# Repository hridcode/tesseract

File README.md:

# Tesseract

Tesseract is a retro-style MP3 player with audio output to speakers and headphones, an LCD display, and battery charging for on-the-go listening. I made this because I wanted to have a dedicated device to run a library of my favorite music in a simplistic way, as a sort of action against streaming services.

## Features

- 32-bit 48kHz stereo output to speakers and headphones
- microSD card file loading (up to 32GB)
- 2.0" LCD display (ST7789)
- Battery charging with power path
- Album and artist shuffling modes
- Genre tags

## Pictures

|Schematic|PCB|Case|
|---|---|---|
||||

## BOM

|Part|Quantity|Cost|Link|
|---|---|---|---|
|0402 4.7uF capacitor|3|$0.070|[LCSC](https://www.lcsc.com/product-detail/C23733.html)|
|0402 10uF capacitor|10|$0.258|[LCSC](https://www.lcsc.com/product-detail/C15525.html)|
|0603 22uF capacitor|3|$0.094|[LCSC](https://www.lcsc.com/product-detail/C59461.html)|
|0402 0.1uF capacitor|18|$0.099|[LCSC](https://www.lcsc.com/product-detail/C1525.html)|
|0402 2.2uF capacitor|4|$0.026|[LCSC](https://www.lcsc.com/product-detail/C12530.html)|
|0402 0.47uF capacitor|2|$0.028|[LCSC](https://www.lcsc.com/product-detail/C47339.html)|
|0402 20pF capacitor|2|$0.016|[LCSC](https://www.lcsc.com/product-detail/C1554.html)|
|0402 1uF capacitor|1|$0.012|[LCSC](https://www.lcsc.com/product-detail/C52923.html)|
|microSD card receptacle|1|$0.061|[LCSC](https://www.lcsc.com/product-detail/C7529389.html)|
|0402 3.3uH inductor|1|$0.076|[LCSC](https://www.lcsc.com/product-detail/C48946153.html)|
|0402 1uH inductor|1|$0.035|[LCSC](https://www.lcsc.com/product-detail/C22400378.html)|
|0402 5.1KΩ resistor|2|$0.005|[LCSC](https://www.lcsc.com/product-detail/C25905.html)|
|0402 470Ω resistor|2|$0.010|[LCSC](https://www.lcsc.com/product-detail/C25117.html)|
|0603 20KΩ resistor|2|$0.008|[LCSC](https://www.lcsc.com/product-detail/C4184.html)|
|0402 10Ω resistor|1|$0.003|[LCSC](https://www.lcsc.com/product-detail/C25077.html)|
|0402 10KΩ resistor|4|$0.019|[LCSC](https://www.lcsc.com/product-detail/C25531.html)|
|0603 27Ω resistor|2|$0.007|[LCSC](https://www.lcsc.com/product-detail/C25190.html)|
|0402 33Ω resistor|1|$0.008|[LCSC](https://www.lcsc.com/product-detail/C25105.html)|
|0402 1KΩ resistor|2|$0.008|[LCSC](https://www.lcsc.com/product-detail/C11702.html)|
|0603 2Ω resistor|2|$0.006|[LCSC](https://www.lcsc.com/product-detail/C22977.html)|
|USB-C receptacle|1|$0.172|[LCSC](https://www.lcsc.com/product-detail/C165948.html)|
|12-pin 0.5mm pitch FPC connector|1|$0.088|[LCSC](https://www.lcsc.com/product-detail/C51901313.html)|
|ST7789 12-pin display|1|$4.060|[AliExpress](https://www.aliexpress.us/item/3256810577766519.html)|
|RP2354A|1|$1.318|[LCSC](https://www.lcsc.com/product-detail/C41378174.html)|
|PCM5102A|1|$1.416|[LCSC](https://www.lcsc.com/product-detail/C107671.html)|
|PAM8403D|1|$0.267|[LCSC](https://www.lcsc.com/product-detail/C5122557.html)|
|PJ-242 switching audio jack|1|$0.138|[LCSC](https://www.lcsc.com/product-detail/C431536.html)|
|8Ω 0.5W 20mm speaker|1|$2.690|[AliExpress](https://www.aliexpress.us/item/3256809939513877.html)|
|IP5306|1|$0.299|[LCSC](https://www.lcsc.com/product-detail/C181692.html)|
|XC6206P332MR|1|$0.147|[LCSC](https://www.lcsc.com/product-detail/C5446.html)|
|3.7V 2000mAh lithium polymer battery|1|$6.990|[AliExpress](https://www.aliexpress.us/item/3256802733222186.html)|
|AS5600-ASOT|1|$1.436|[LCSC](https://www.lcsc.com/product-detail/C499458.html)|
|Diametric magnet|1|$0.199|[AliExpress](https://www.aliexpress.us/item/3256810578708839.html)|
|2x1mm neodymium magnets|50|$3.220|[AliExpress](https://www.aliexpress.us/item/3256811645736463.html)|
|12MHz 20pF crystal oscillator|1|$0.096|[LCSC](https://www.lcsc.com/product-detail/C9002.html)|
|3-pin SPDT slide switch|1|$4.950|[AliExpress](https://www.aliexpress.us/item/3256809632258636.html)|
|PCB|1|$1.400|[JLCPCB](https://cart.jlcpcb.com/quote?stencilLayer=4&stencilWidth=65&stencilLength=100&stencilCounts=5&plateType=1&spm=Jlcpcb.Homepage.1010)|
|Resin printed parts|5|$8.640|[JLC3DP](https://jlc3dp.com/3d-printing-quote?queryMaterialTechnicsId=1)|
|**Total**||**$40.166**||

## Notes

You can visit the Onshape project [here](https://cad.onshape.com/documents/0cda69ddcaf8f9abaf0bc503/w/b4a9e0f35602d26ad8b0afbe/e/33b76f34621fe33578d60277?renderMode=0&uiState=6a938bd5edeed672aad4ec0b).

The PCB is 4 layers (SIG/GND/PWR/SIG).

The firmware is still being developed. I will work on making it better once the device is fully built.

I plan on getting this assembled, hopefully it's not too expensive :(

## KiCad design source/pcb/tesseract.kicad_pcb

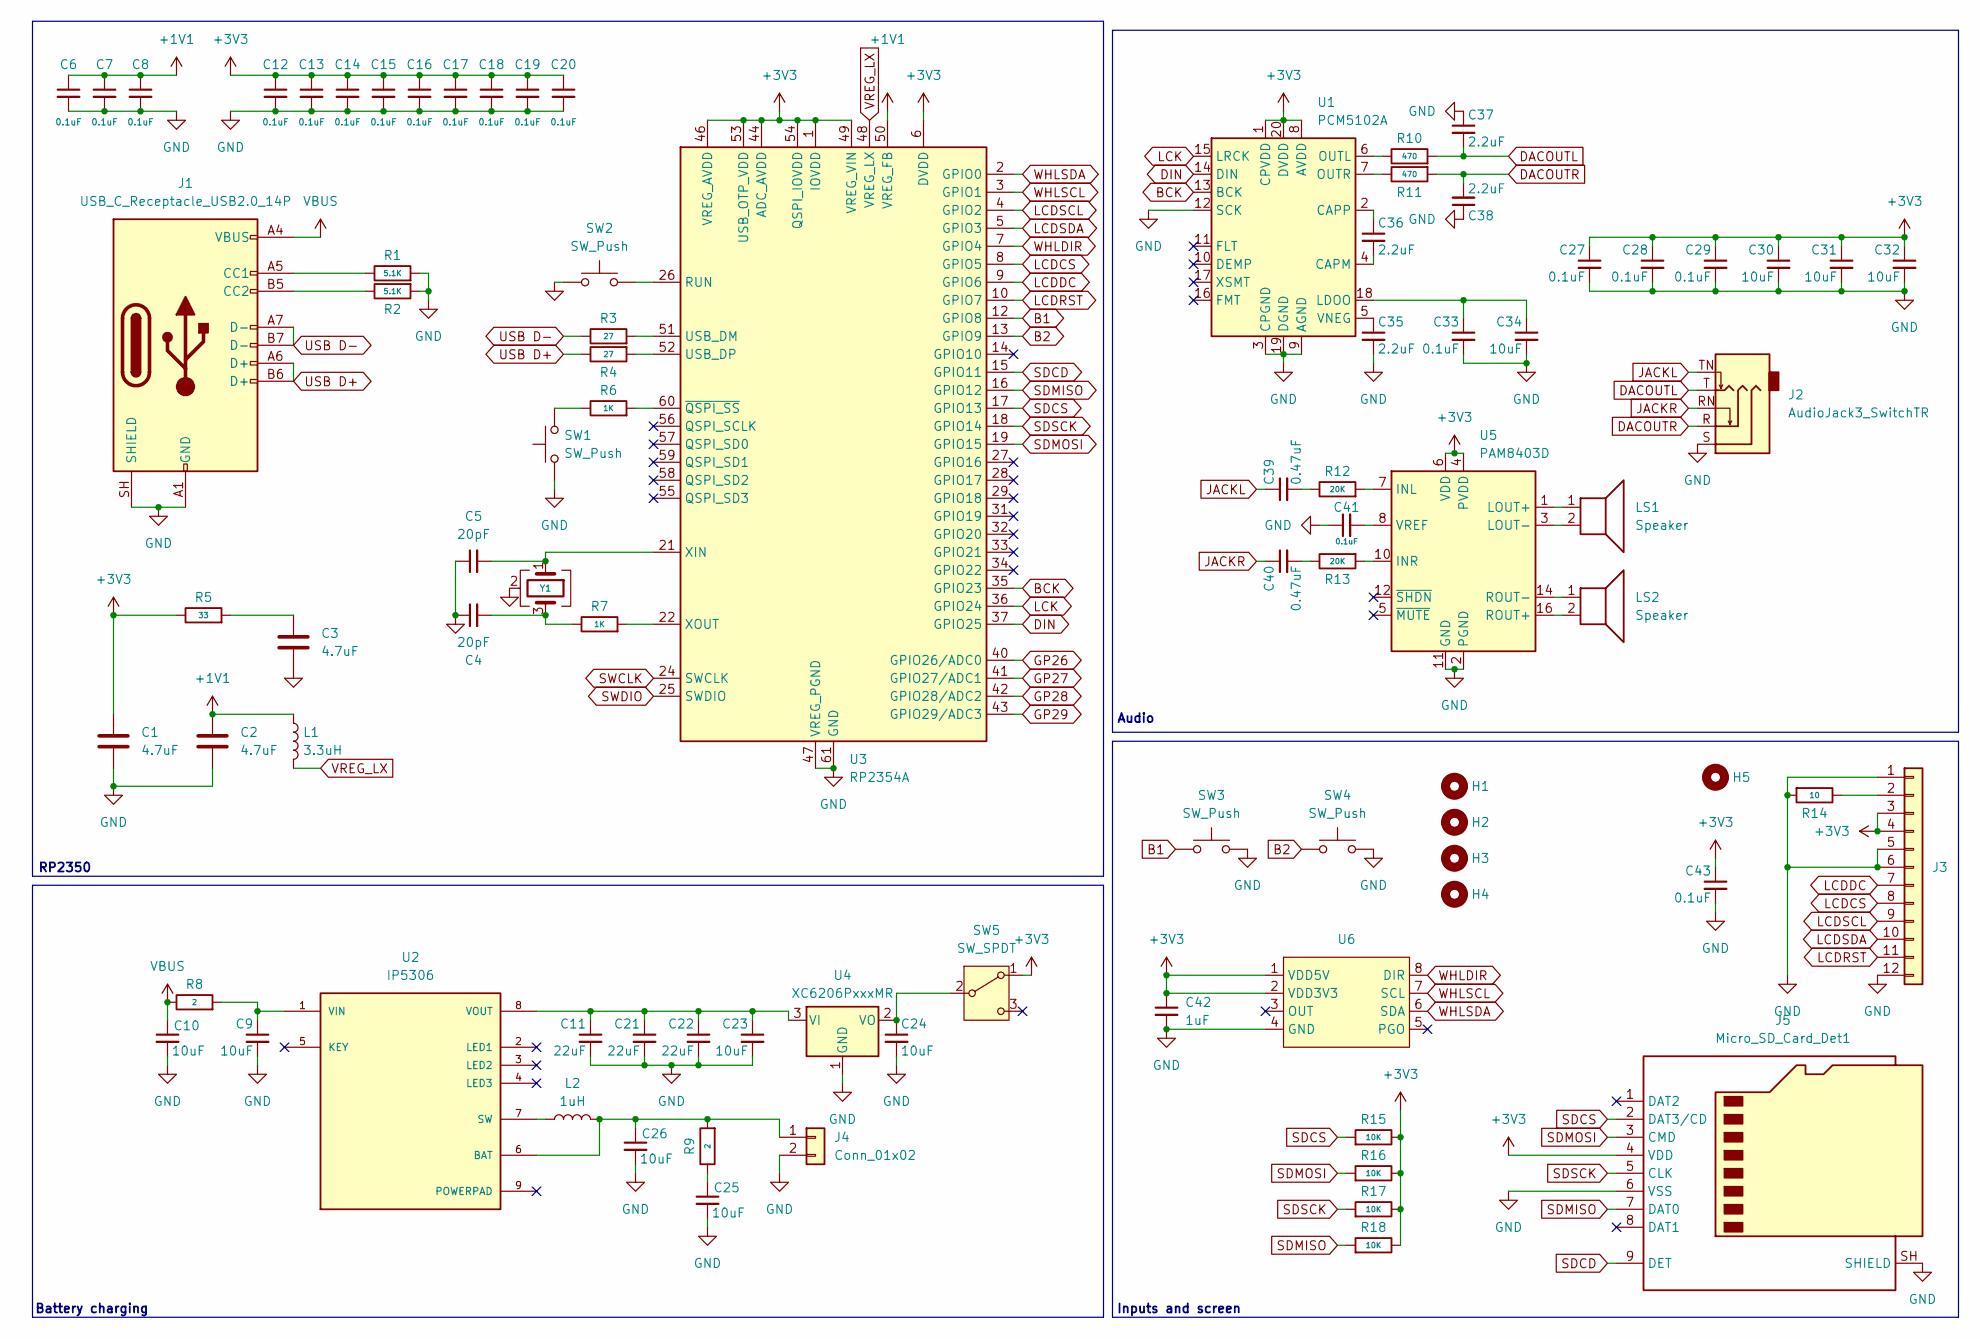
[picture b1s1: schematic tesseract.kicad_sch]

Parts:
C1, C2, C3: 4.7uF; C_0402_1005Metric; MPN C23733
C4, C5: 20pF; C_0402_1005Metric; MPN C1554
C6, C7, C8, C12, C13, C14, C15, C16, C17, C18, C19, C20, C27, C28, C29, C33: 0.1uF; C_0402_1005Metric; MPN C1525
C9, C10, C23, C24, C25, C26, C30, C31, C32, C34: 10uF; C_0402_1005Metric; MPN C15525
C11, C21, C22: 22uF; C_0603_1608Metric; MPN C59461
C35, C36, C37, C38: 2.2uF; C_0402_1005Metric; MPN C12530
C39, C40: 0.47uF; C_0402_1005Metric; MPN C1525
C41: 0.1uF; C_0402_1005Metric
C42: 1uF; C_0402_1005Metric
C43: 0.1uF; C_0402_1005Metric; MPN C15525
H1, H2, H3, H4: MountingHole; MountingHole_3.2mm_M3
H5: MountingHole; display_hole
J1: USB_C_Receptacle_USB2.0_14P; USB_C_Receptacle_HRO_TYPE-C-31-M-12; MPN C165948
J2: AudioJack3_SwitchTR; AUDIO-SMD_PJ-242_1
J3: Conn_01x12; Hirose_FH12-12S-0.5SH_1x12-1MP_P0.50mm_Horizontal
J4: Conn_01x02; PinHeader_1x02_P2.54mm_Vertical
J5: Micro_SD_Card_Det1; TF-SMD_TF-CARD-H1.8
L1: 3.3uH; L_0402_1005Metric; MPN C84474
L2: 1uH; L_0402_1005Metric; MPN C84468
LS1, LS2: Speaker; PinHeader_1x02_P2.54mm_Vertical
R1, R2: 5.1K; R_0402_1005Metric; MPN C25905
R3, R4: 27; R_0603_1608Metric; MPN C25190
R5: 33; R_0402_1005Metric; MPN C25105
R6, R7: 1K; R_0402_1005Metric; MPN C11702
R8, R9: 2; R_0603_1608Metric; MPN C22977
R10, R11: 470; R_0402_1005Metric; MPN C25117
R12, R13: 20K; R_0603_1608Metric; MPN C25190
R14: 10; R_0402_1005Metric; MPN C11702
R15, R16, R17, R18: 10K; R_0402_1005Metric; MPN C11702
SW1, SW2: SW_Push; L_Taiyo-Yuden_NR-40xx
SW3, SW4: SW_Push; button_342
SW5: SW_SPDT; SW-TH_MSK12D18G2
U1: PCM5102A; TSSOP-20_4.4x6.5mm_P0.65mm; MPN C107671
U2: IP5306; eSOP-8; PARTREV 1.31
U3: RP2354A; QFN-60-1EP_7x7mm_P0.4mm_EP3.4x3.4mm
U4: XC6206PxxxMR; SOT-23-3; MPN C5446
U5: PAM8403D; SOIC-16_3.9x9.9mm_P1.27mm
U6: SOIC-8-1EP_3.9x4.9mm_P1.27mm_EP2.29x3mm_ThermalVias
Y1: Crystal_GND24; Crystal_SMD_3225-4Pin_3.2x2.5mm; MPN C9002

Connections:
+1V1: C2.1, C6.1, C7.1, C8.1, L1.1, U3.50 (VREG_FB)
+3V3: C1.1, C12.1, C13.1, C14.1, C15.1, C16.1, C17.1, C18.1, C19.1, C20.1, C27.1, C28.1, C29.1, C30.1, C31.1, C32.1, C42.1, C43.1, J3.3, J3.4, J5.4 (VDD), R5.1, R15.1, R16.1, R17.1, R18.1, SW5.1 (A), U1.1 (CPVDD), U1.8 (AVDD), U1.20 (DVDD), U3.1 (IOVDD), U3.6 (DVDD), U3.11 (IOVDD), U3.20 (IOVDD), U3.23 (DVDD), U3.30 (IOVDD), U3.38 (IOVDD), U3.39 (DVDD), U3.44 (ADC_AVDD), U3.45 (IOVDD), U3.46 (VREG_AVDD), U3.49 (VREG_VIN), U3.53 (USB_OTP_VDD), U3.54 (QSPI_IOVDD), U5.4 (PVDD), U5.6 (VDD), U5.13 (PVDD), U6.1 (VDD5V), U6.2 (VDD3V3)
B1: SW3.1, U3.12 (GPIO8)
B2: SW4.1, U3.13 (GPIO9)
BCK: U1.13 (BCK), U3.35 (GPIO23)
DACOUTL: C37.2, J2.T, R10.2
DACOUTR: C38.2, J2.R, R11.2
DIN: U1.14 (DIN), U3.37 (GPIO25)
GND: C1.2, C2.2, C3.2, C4.1, C5.1, C6.2, C7.2, C8.2, C9.2, C10.2, C11.2, C12.2, C13.2, C14.2, C15.2, C16.2, C17.2, C18.2, C19.2, C20.2, C21.2, C22.2, C23.2, C24.2, C25.2, C26.2, C27.2, C28.2, C29.2, C30.2, C31.2, C32.2, C33.2, C34.2, C35.2, C37.1, C38.1, C41.1, C42.2, C43.2, J1.A1 (GND), J1.A12 (GND), J1.B1 (GND), J1.B12 (GND), J1.SH (SHIELD), J2.S, J3.1, J3.5, J3.6, J3.12, J4.2, J5.6 (VSS), J5.SH (SHIELD), R1.2, R2.2, R14.2, SW1.1, SW2.1, SW3.2, SW4.2, U1.3 (CPGND), U1.9 (AGND), U1.12 (SCK), U1.19 (DGND), U3.47 (VREG_PGND), U3.61 (GND), U4.1 (GND), U5.2 (PGND), U5.11 (GND), U5.15 (PGND), U6.4 (GND), Y1.2 (G), Y1.4 (G)
GP26: U3.40 (GPIO26/ADC0)
GP27: U3.41 (GPIO27/ADC1)
GP28: U3.42 (GPIO28/ADC2)
GP29: U3.43 (GPIO29/ADC3)
JACKL: C39.1, J2.TN
JACKR: C40.1, J2.RN
LCDCS: J3.8, U3.8 (GPIO5)
LCDDC: J3.7, U3.9 (GPIO6)
LCDRST: J3.11, U3.10 (GPIO7)
LCDSCL: J3.9, U3.4 (GPIO2)
LCDSDA: J3.10, U3.5 (GPIO3)
LCK: U1.15 (LRCK), U3.36 (GPIO24)
unnamed: C3.1, R5.2
unnamed: C4.2, R7.1, Y1.3
unnamed: C25.1, R9.1
unnamed: C39.2, R12.1
unnamed: C40.2, R13.1
unnamed: J1.A5 (CC1), R1.1
unnamed: J1.B5 (CC2), R2.1
unnamed: J3.2, R14.1
unnamed: C26.1, J4.1, L2.2, R9.2, U2.6 (BAT)
unnamed: R6.1, SW1.2
unnamed: C24.1, SW5.2 (B), U4.2 (VO)
unnamed: C36.2, U1.4 (CAPM)
unnamed: C36.1, U1.2 (CAPP)
unnamed: C33.1, C34.1, U1.18 (LDOO)
unnamed: R10.1, U1.6 (OUTL)
unnamed: R11.1, U1.7 (OUTR)
unnamed: C35.1, U1.5 (VNEG)
unnamed: L2.1, U2.7 (SW)
unnamed: C9.1, R8.2, U2.1 (VIN)
unnamed: C11.1, C21.1, C22.1, C23.1, U2.8 (VOUT), U4.3 (VI)
unnamed: SW2.2, U3.26 (RUN)
unnamed: R3.2, U3.51 (USB_DM)
unnamed: R4.2, U3.52 (USB_DP)
unnamed: C5.2, U3.21 (XIN), Y1.1
unnamed: R7.2, U3.22 (XOUT)
unnamed: R6.2, U3.60 (~QSPI_SS)
unnamed: R12.2, U5.7 (INL)
unnamed: R13.2, U5.10 (INR)
unnamed: LS1.1, U5.1 (LOUT+)
unnamed: LS1.2, U5.3 (LOUT-)
unnamed: LS2.2, U5.16 (ROUT+)
unnamed: LS2.1, U5.14 (ROUT-)
unnamed: C41.2, U5.8 (VREF)
SDCD: J5.9 (DET), U3.15 (GPIO11)
SDCS: J5.2 (DAT3/CD), R15.2, U3.17 (GPIO13)
SDMISO: J5.7 (DAT0), R18.2, U3.16 (GPIO12)
SDMOSI: J5.3 (CMD), R16.2, U3.19 (GPIO15)
SDSCK: J5.5 (CLK), R17.2, U3.18 (GPIO14)
SWCLK: U3.24 (SWCLK)
SWDIO: U3.25 (SWDIO)
USB D+: J1.A6 (D+), J1.B6 (D+), R4.1
USB D-: J1.A7 (D-), J1.B7 (D-), R3.1
VBUS: C10.1, J1.A4 (VBUS), J1.A9 (VBUS), J1.B4 (VBUS), J1.B9 (VBUS), R8.1
VREG_LX: L1.2, U3.48 (VREG_LX)
WHLDIR: U3.7 (GPIO4), U6.8 (DIR)
WHLSCL: U3.3 (GPIO1), U6.7 (SCL)
WHLSDA: U3.2 (GPIO0), U6.6 (SDA)

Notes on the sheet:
Audio
Battery charging
Inputs and screen
RP2350

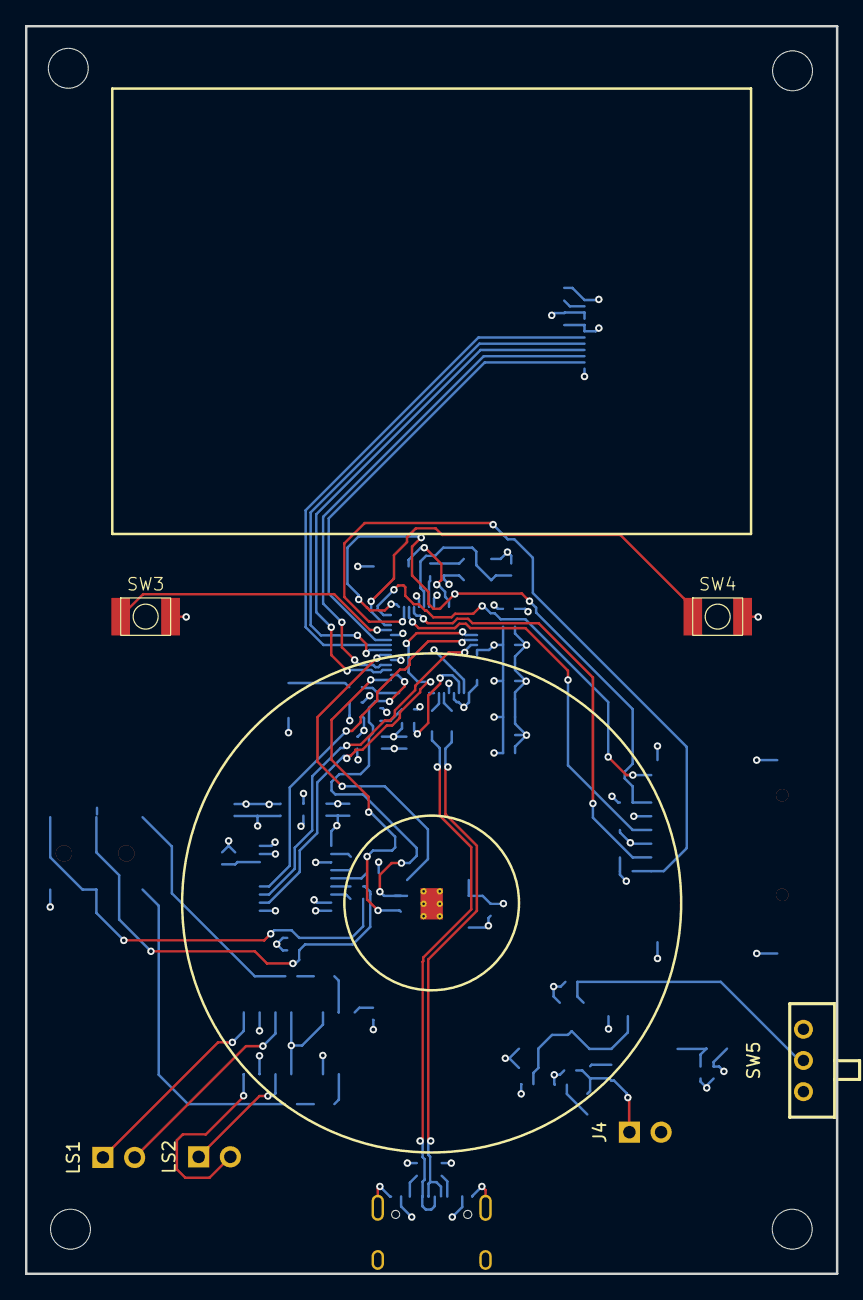
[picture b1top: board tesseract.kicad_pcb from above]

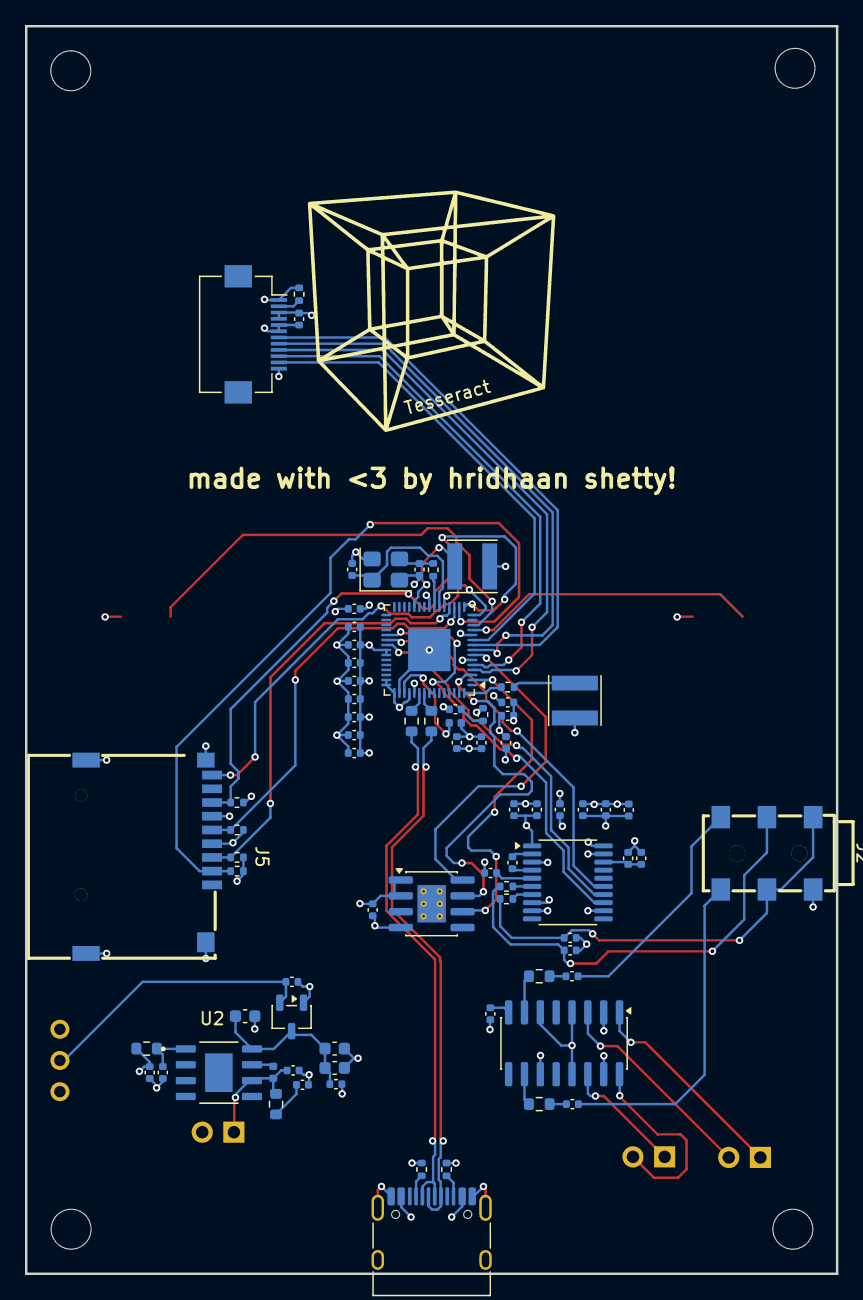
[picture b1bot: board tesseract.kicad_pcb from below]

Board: 4 copper layers, 65.0 x 100.0 mm, 87 parts (76 on the bottom side), 62 nets.
